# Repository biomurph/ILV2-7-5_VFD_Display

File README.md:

# ILV2-7-5_VFD_Display
KiCAD circuit for a VFD Clock using the Popular ILV2-7/5 flat tube segmented nixie tube thingie

Not sure if [this link](https://www.ebay.com/itm/Lot-of-20-IVL2-7-5-IVL-VFD-DIGIT-CLOCK-DISPLAY-TUBE-GREEN-Tube-New-FREE-SHIPPING/252890205246?_trkparms=aid%3D222007%26algo%3DSIM.MBE%26ao%3D2%26asc%3D41375%26meid%3Dbe2e339f0da54301a07820f89799816e%26pid%3D100623%26rk%3D3%26rkt%3D6%26sd%3D192058830857&_trksid=p2047675.c100623.m-1) still works

This work is greatly indebted to work that came before. Namely
[Callum Nunez-Vas](https://callumnunesvaz.wordpress.com/) and his [Dogbone Watch](https://callumnunesvaz.wordpress.com/portfolio/dogbonevfd/) which is also based on the [cyberpunk wristwatch](http://www.johngineer.com/blog/?p=1595) by [johngineer](http://www.johngineer.com/blog/).

I made some changes.

First, my uC is a [PIC32MX250F128B](http://www.microchip.com/wwwproducts/en/PIC32MX250F128B), which supports USB OTG, which is nice and it's also Arduino compatible via ChipKIT and Digilent's [DP32](http://chipkit.net/wiki/index.php?title=ChipKIT_DP32) which makes it nice for sharing.

The other thing that I changed is the oscillator that Callum used to drive the Cathode filament. Callum drives it with a timer on his PIC16F828. I needed more pins, so I decided to make a stand-alone relaxation oscillator built out of a [74HCG214](https://www.mouser.com/ProductDetail/Nexperia/74HC2G14GV125/?qs=sGAEpiMZZMutVWjHE%2fYQwzJv2zzn7Nf7cpkcMgkB%2fH8%3d) dual Schmidtt Trigger Inverter. I set mine up as a dual oscillator clocking at ~1KHz to drive the hours/mimutes Cathodes. 

There's two pushbuttons for interfacing and an LED for control and user feedback. I'm using the same [DS3231](https://www.maximintegrated.com/en/products/digital/real-time-clocks/DS3231.html) that Callum uses, and also the [MAX6920](https://www.maximintegrated.com/en/products/power/display-power-control/MAX6920.html) for the high voltage SIPO to drive the segments.

It's pretty basic beyond that. The power supply is based on the Dogbone, but I'm using a 3V0 regulator instead of a 3V3 and I have a V-divider set up as a battery level sensor that the PIC can read. 

* Maximum input Voltage 6V
* Minimum input Voltage 3.0V
* Current with VFD DISABLED ~26mA
* Current with VFD ENABLED showing all 8s ~150mA

# Push Button Control

## Test Battery Level
Press Switch 2 once. The screen will print a lowercase `b` and then the voltage level with 0.01mV resolution. Press again to go back to time display.

## Change Time
Press Switch 1 once. Hour will blink. Press Switch 2 to increment hour.

Press Switch 1 again. Minute will blink. Press Switch 2 to increment minute.

Press Switch 1 again. Display will show option between 24 hour and 12 hour time. Press Switch 2 to toggle between 24h and 12h.

Press Switch 1 again to go back to the time display.

# Power & Charging

Switch 4 is the reset switch to the PIC. When you press it, the micro-contoller resets. It will start in 24 hour mode.

The thing runs on a high capacity LiPo battery. Plug it into a micro USB cable for charging. You can also program the PIC through the USB connection if you want to.

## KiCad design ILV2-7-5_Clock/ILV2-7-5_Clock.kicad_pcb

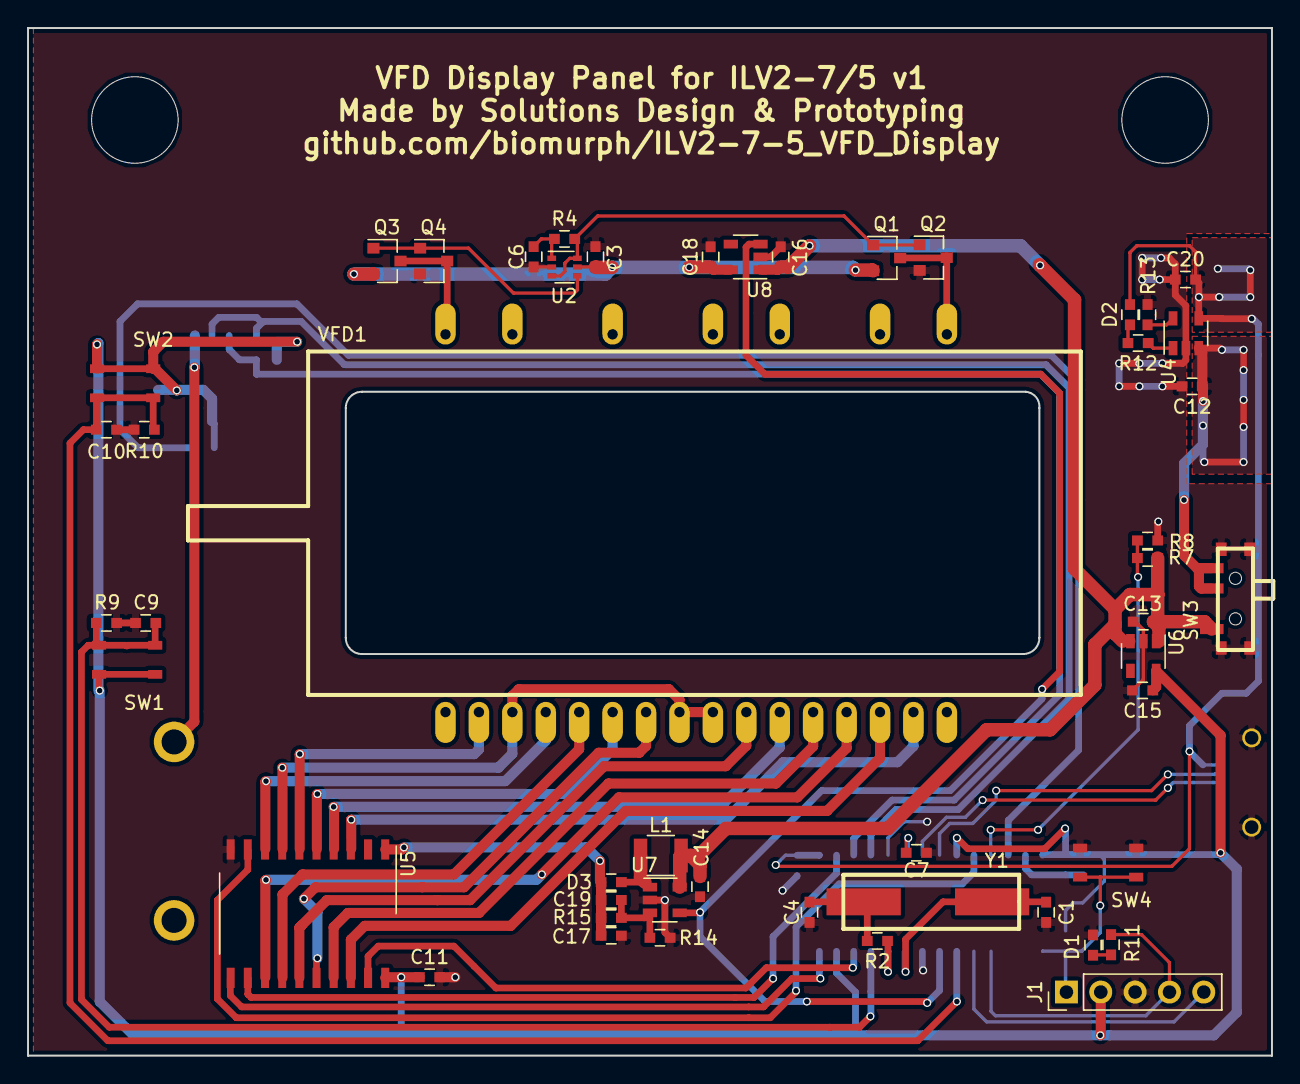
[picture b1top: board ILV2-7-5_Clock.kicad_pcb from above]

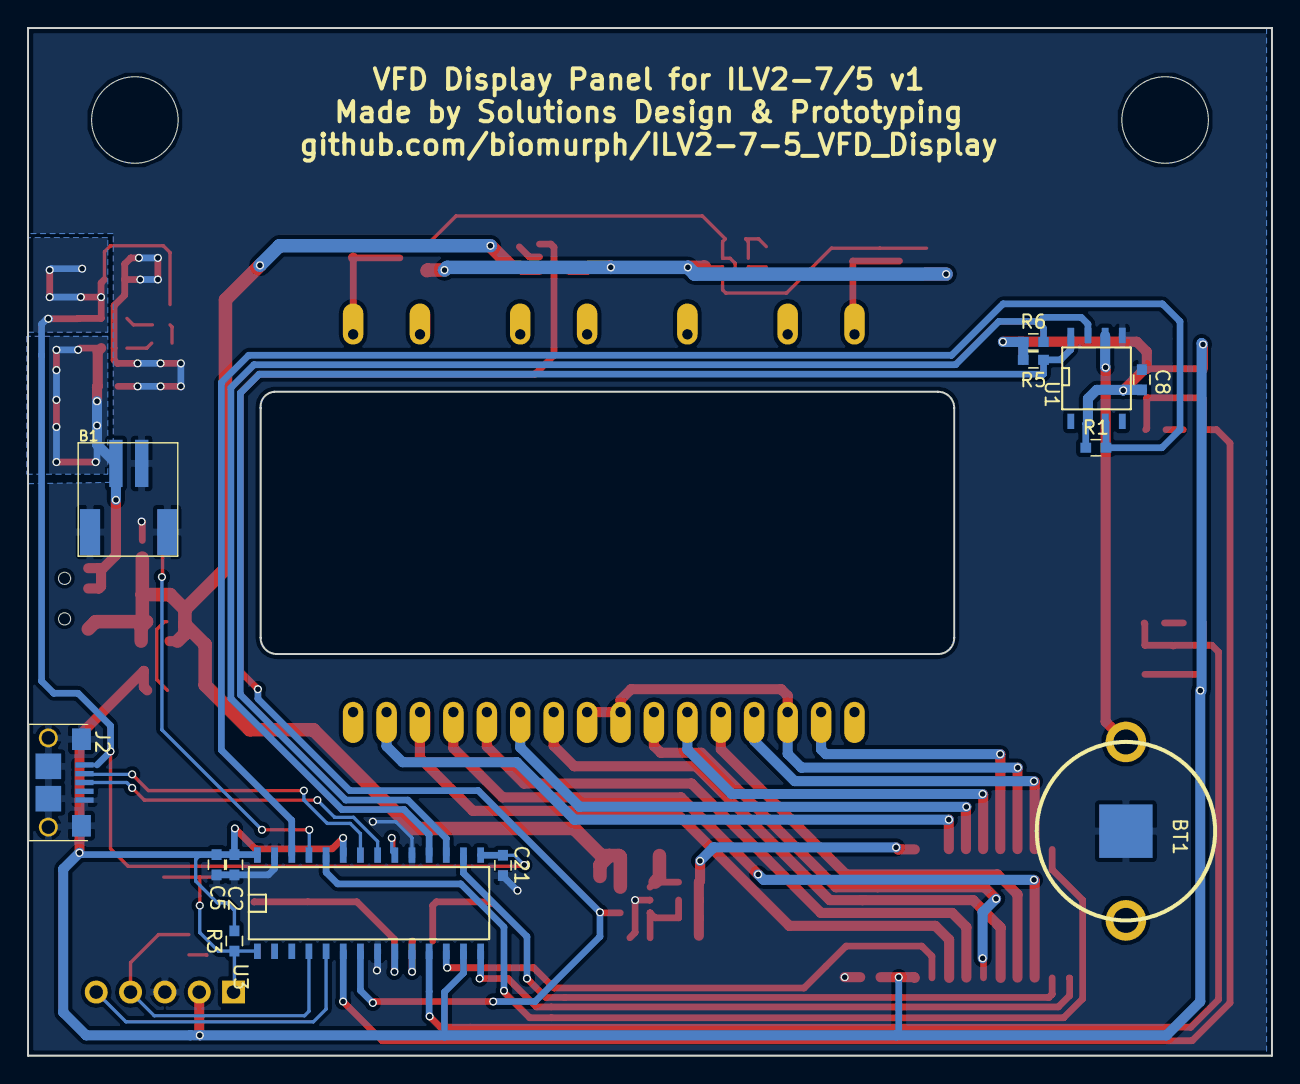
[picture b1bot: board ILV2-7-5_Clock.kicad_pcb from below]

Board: 2 copper layers, 92.0 x 76.0 mm, 62 parts (13 on the bottom side), 51 nets.

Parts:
B1: JS_2_Battery; JST_RA_SMT
BT1: Battery_Cell; 12BH062-GR
C1, C4: 18pF; C_0603
C2, C13, C15, C16, C18, C21: 1uF; C_0603
C3, C5, C8, C9, C10, C11: 0.1uF; C_0603
C6: 0.15uF; C_0603
C7, C12, C20: 10uF; C_0603
C14: 22uF 6.3V; C_0603
C17: 4.7uF 50V; C_0603
C19: 470pF 50V; C_0603
D1, D2: LED; C_0603
D3: 500mA 30V; C_0603
J1: CONN_01X05; Pin_Header_Straight_1x05_Pitch2.54mm
J2: USB_OTG; 10118193_microUSB
L1: 10uH 1.2A; C_1210
Q1, Q3: BSS84; SOT-23
Q2, Q4: BSS138; SOT-23
R1, R4, R5, R6, R9, R10: 10k; C_0603
R2: 680R; C_0603
R3, R14: 10K; C_0603
R7, R8: 100K; C_0603
R11: 1k; C_0603
R12: 1K; C_0603
R13: R; C_0603
R15: 150K; C_0603
SW1, SW2, SW4: TACT_SWITCH; PTS810
SW3: PCM12SMTR
U1: DS3231M; SOIC-8-N
U2: 74HC2G14; SOT-363_SC-70-6
U3: PIC32MX250F128B; SOIC-28
U4: MCP73831; SOT-23-5
U5: MAX6920; SO-20_12.8x7.5mm_Pitch1.27mm
U6, U8: MIC5317; SOT-23-5
U7: LMR62421; SOT-23-5
VFD1: ILV2-7/5; IVL2-7-5
Y1: 8MHz; IQD_HC49_XTAL

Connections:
+2V5: C3.1, C18.1, Q1.2, Q3.2, U2.5, U8.5
+3V3: C2.1, C5.1, C8.1, C11.1, C15.1, J1.2, R1.1, R3.2, R5.2, R6.1, SW1.1, SW1.2, SW2.1, SW2.2, U1.2, U3.13, U3.23, U3.28, U5.20, U6.5
+5V: C20.2, C21.2, D2.2, J2.1, U3.15, U4.4
+24V: C17.1, C19.1, D3.1, R15.1, U5.1
/BAT_CHRG: B1.1, C12.1, SW3.2, SW3.3, U4.3
/BAT_SENS: R7.1, R8.2, U3.25
/BLANK: U3.24, U5.9
/BOOT_EN: C9.1, R9.2, SW1.3, SW1.4, U3.11
/CATHODE_AB: Q1.3, Q2.3, VFD1.17
/CATHODE_CD: Q3.3, Q4.3, VFD1.23
/CLK: U3.14, U5.11
/D+: J2.3, U3.21
/D-: J2.2, U3.22
/DIN: U3.12, U5.19
/DOT: U5.7, VFD1.3, VFD1.8, VFD1.9
/GRID_1: U5.6, VFD1.2
/GRID_2: U5.5, VFD1.6
/GRID_4: U5.4, VFD1.11
/GRID_5: U5.3, VFD1.15
/H_BridgeA: Q1.1, Q2.1, R4.2, U2.3, U2.6
/H_BridgeB: Q3.1, Q4.1, U2.4
/INT/SQW: R1.2, U1.3, U3.26
/LOAD: U3.16, U5.12
/MCLR: J1.1, R3.1, SW4.1, SW4.2, U3.1
/PGC: J1.5, U3.5
/PGD: D1.2, J1.4, U3.4
/SCL: R5.1, U1.8, U3.17
/SDA: R6.2, U1.7, U3.18
/SWITCH_1: C10.1, R10.2, SW2.3, SW2.4, U3.6
/VFD_EN: U3.7, U7.4, U8.3
/V_BAT: C13.1, C14.1, C16.1, L1.2, R7.2, SW3.1, U6.1, U6.3, U7.5, U8.1
/a: U5.18, VFD1.14
/b: U5.17, VFD1.12
/c: U5.16, VFD1.7
/d: U5.15, VFD1.10
/e: U5.14, VFD1.5
/f: U5.13, VFD1.13
/g: U5.8, VFD1.4
GND: B1.2, B1.3, B1.4, BT1.2, C1.2, C2.2, C3.2, C4.2, C5.2, C6.2, C7.2, C8.2, C9.2, C10.2, C11.2, C12.2, C13.2, C14.2, C15.2, C16.2, C17.2, C18.2, C20.1, C21.1, J1.3, J2.5, J2.6, J2.7, J2.8, J2.9, J2.10, J2.11, Q2.2, Q4.2, R8.1, R9.1, R10.1, R11.1, R13.2, R14.2, SW3.4, SW3.5, SW3.6, SW3.7, SW4.3, SW4.4, U1.5, U2.2, U3.8, U3.19, U3.27, U4.2, U5.10, U6.2, U7.2, U8.2
unnamed: BT1.1, U1.6
unnamed: C1.1, U3.9, Y1.1
unnamed: C4.1, R2.2, Y1.2
unnamed: C6.1, R4.1, U2.1
unnamed: C7.1, U3.20
unnamed: C19.2, R14.1, R15.2, U7.3
unnamed: D1.1, R11.2
unnamed: D2.1, R12.2
unnamed: D3.2, L1.1, U7.1
unnamed: R2.1, U3.10
unnamed: R12.1, U4.1
unnamed: R13.1, U4.5

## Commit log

2017-11-12 Completed schematic and first pass of PCB layout
2017-11-12 Small update
2017-11-15 More progress on the PCB and casing down schem issues
2017-11-20 Finished first draft of pub and zone fills
2017-11-20 Added mount holes, fixed the inductor footprint size
2017-11-28 Some more such
2017-11-28 Readme updated, etc
2017-12-04 Added BOM
    Needs update of some component footprints
2017-12-11 Added specs to readme
2018-04-13 Updated readme with how to guide
2018-04-13 readme update
2018-04-16 CHANGED FROM BATTERY TO 24V SUPPLY
2019-03-04 Updated Schematic with parts for desk clock
2019-03-18 re routed the board. added new footprints
2020-06-15 Minor Changes
